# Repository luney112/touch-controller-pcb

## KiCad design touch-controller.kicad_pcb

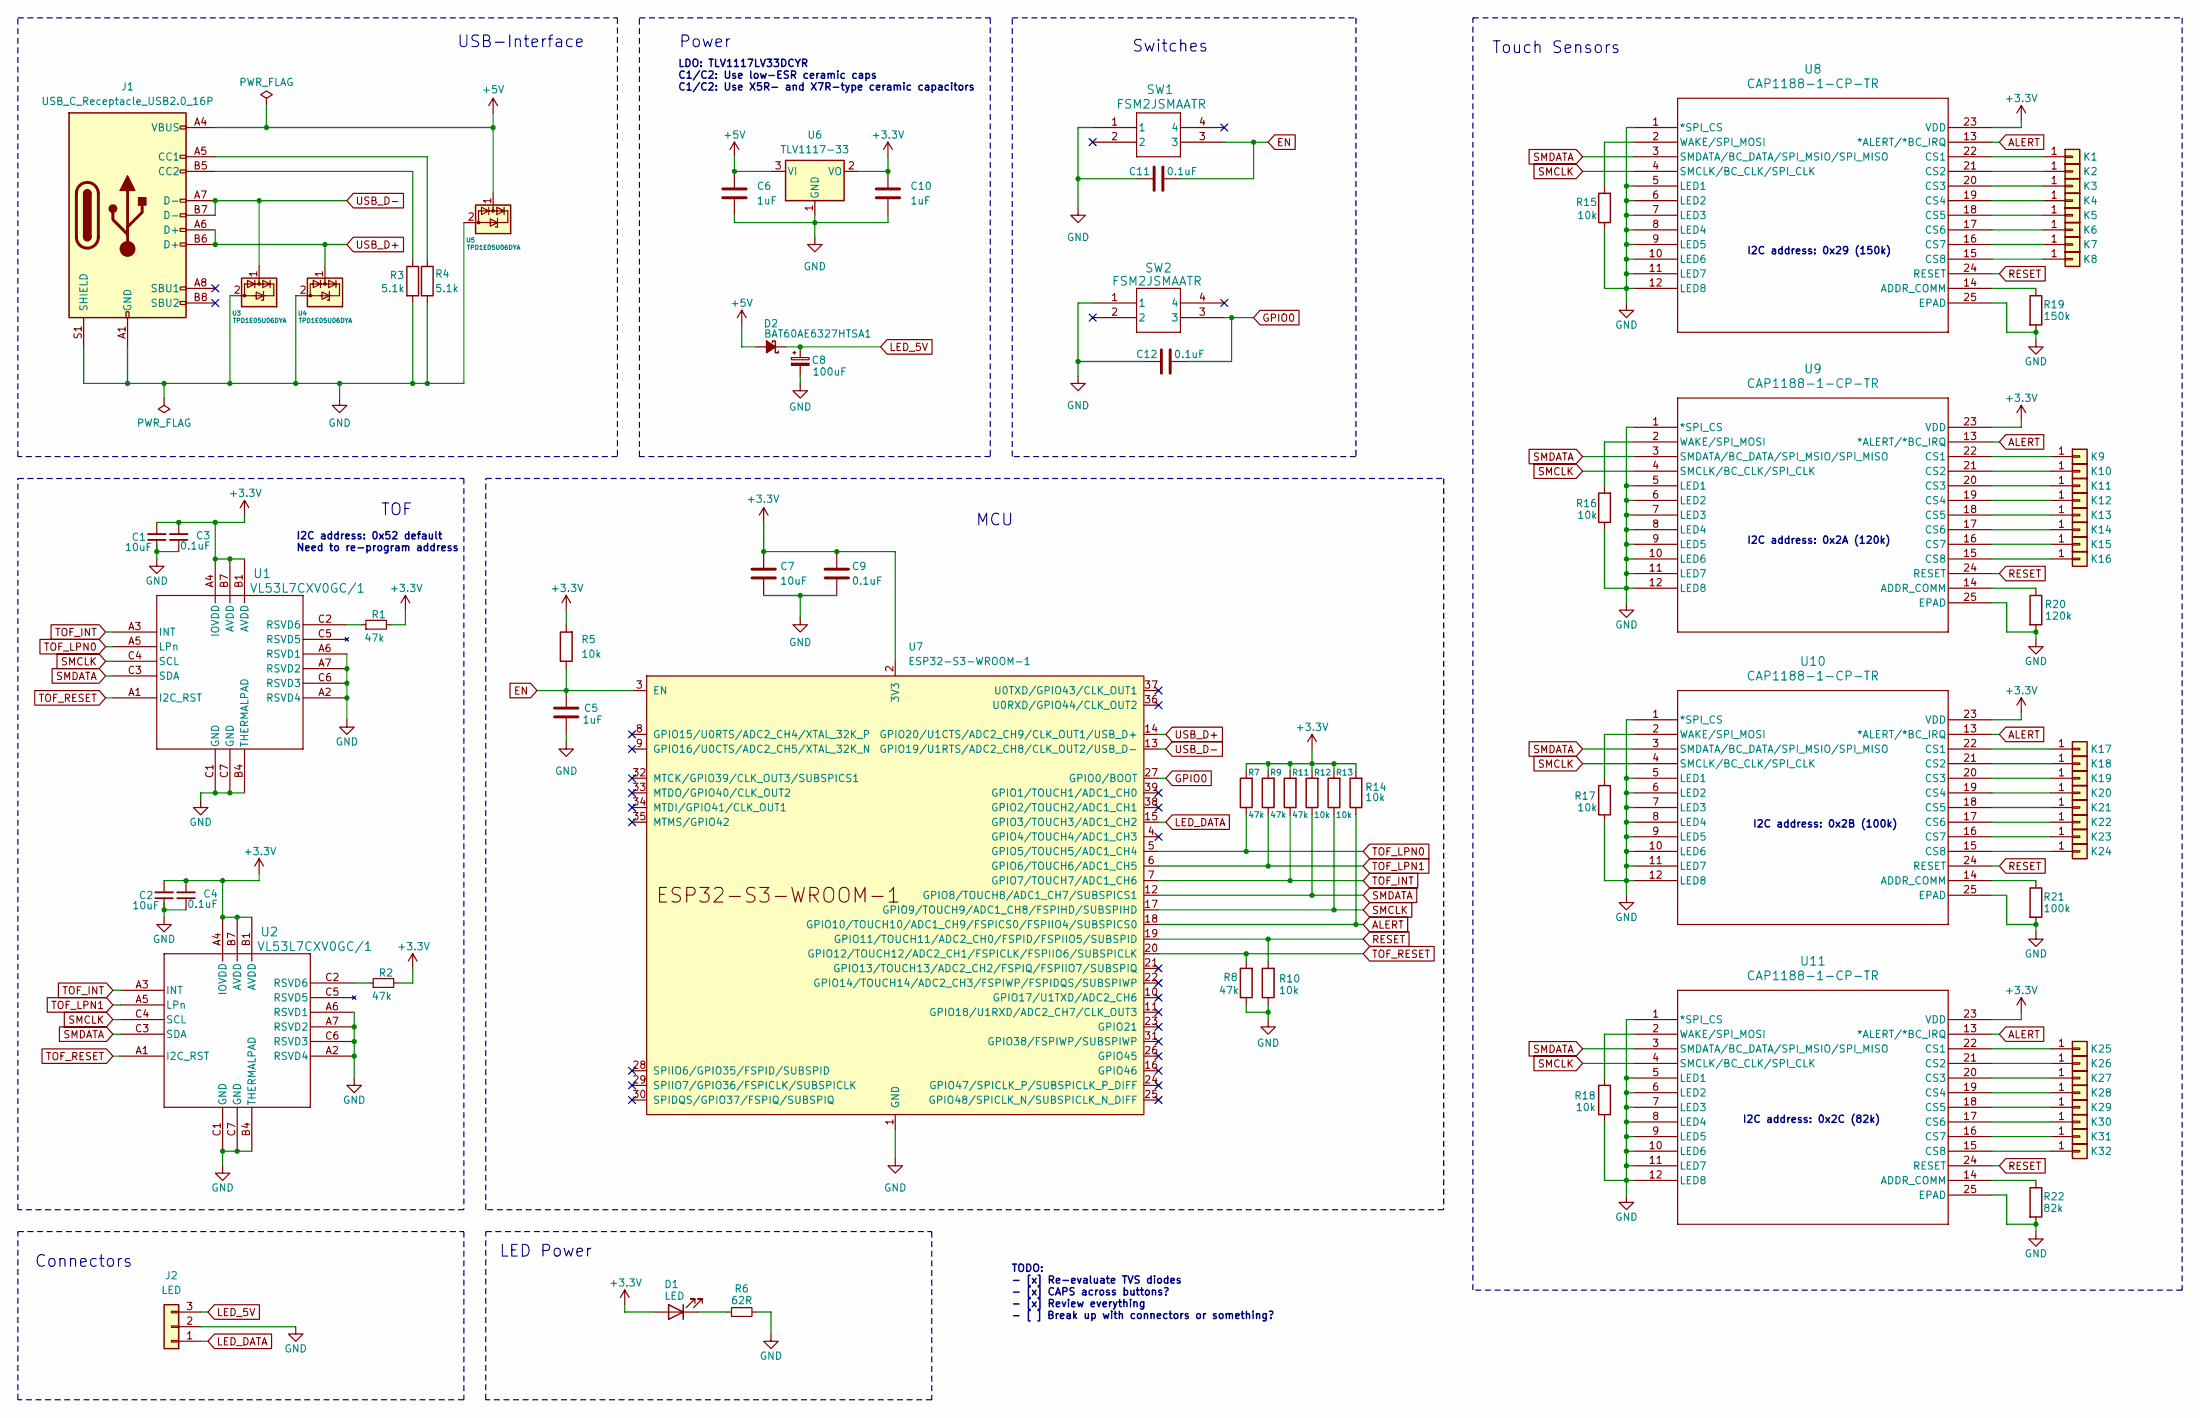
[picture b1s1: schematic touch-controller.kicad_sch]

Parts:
C1, C2, C7: 10uF; C_0805_2012Metric_Pad1.18x1.45mm_HandSolder
C3, C4, C9, C11, C12: 0.1uF; C_0805_2012Metric_Pad1.18x1.45mm_HandSolder
C5, C6, C10: 1uF; C_0805_2012Metric_Pad1.18x1.45mm_HandSolder
C8: 100uF; CP_Elec_6.3x5.8
D1: LED; LED_0805_2012Metric_Pad1.15x1.40mm_HandSolder
D2: BAT60AE6327HTSA1; D_SOD-323_HandSoldering
J1: USB_C_Receptacle_USB2.0_16P; USB_C_Receptacle_GCT_USB4105-xx-A_16P_TopMnt_Horizontal
J2: LED; SolderWire-0.75sqmm_1x03_P4.8mm_D1.25mm_OD2.3mm_Relief
K1, K2, K3, K4, K5, K6, K7, K8, K9, K10, K11, K12, K13, K14, K15, K16, K17, K18, K19, K20, K21, K22, K23, K24, K25, K26, K27, K28, K29, K30, K31, K32: Conn_01x01; TouchKey_Standard
R1, R2, R7, R8, R9, R11: 47k; R_0805_2012Metric_Pad1.20x1.40mm_HandSolder
R3, R4: 5.1k; R_0805_2012Metric_Pad1.20x1.40mm_HandSolder
R5, R10, R12, R13, R14, R15, R16, R17, R18: 10k; R_0805_2012Metric_Pad1.20x1.40mm_HandSolder
R6: 62R; R_0805_2012Metric_Pad1.20x1.40mm_HandSolder
R19: 150k; R_0805_2012Metric_Pad1.20x1.40mm_HandSolder
R20: 120k; R_0805_2012Metric_Pad1.20x1.40mm_HandSolder
R21: 100k; R_0805_2012Metric_Pad1.20x1.40mm_HandSolder
R22: 82k; R_0805_2012Metric_Pad1.20x1.40mm_HandSolder
SW1, SW2: FSM2JSMAATR; SWITCH_FSM2JSMAA_TYC
U1, U2: VL53L7CXV0GC/1; LGA16_OPTICAL-LINER_STM
U3, U4, U5: TPD1E05U06DYA; D_SOD-523
U6: TLV1117-33; SOT-223-3_TabPin2
U7: ESP32-S3-WROOM-1
U8, U9, U10, U11: CAP1188-1-CP-TR; QFN24_4X4MC_MCH

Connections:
+3.3V: C1.2, C2.2, C3.2, C4.2, C7.2, C9.2, C10.1, D1.2 (A), R1.2, R2.2, R5.2, R7.2, R9.2, R11.2, R12.2, R13.2, R14.2, U1.A4 (IOVDD), U1.B1 (AVDD), U1.B7 (AVDD), U2.A4 (IOVDD), U2.B1 (AVDD), U2.B7 (AVDD), U6.2 (VO), U7.2 (3V3), U8.23 (VDD), U9.23 (VDD), U10.23 (VDD), U11.23 (VDD)
+5V: C6.1, D2.2 (A), J1.A4 (VBUS), J1.A9 (VBUS), J1.B4 (VBUS), J1.B9 (VBUS), U5.1 (I/O), U6.3 (VI)
ALERT: R14.1, U7.18 (GPIO10/TOUCH10/ADC1_CH9/FSPICS0/FSPIIO4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), U8.13 (*ALERT/*BC_IRQ), U9.13 (*ALERT/*BC_IRQ), U10.13 (*ALERT/*BC_IRQ), U11.13 (*ALERT/*BC_IRQ)
EN: C5.1, C11.1, R5.1, SW1.3, U7.3 (EN)
GND: C1.1, C2.1, C3.1, C4.1, C5.2, C6.2, C7.1, C8.2, C9.1, C10.2, C11.2, C12.2, J1.A1 (GND), J1.A12 (GND), J1.B1 (GND), J1.B12 (GND), J1.S1 (SHIELD), J2.2, R3.2, R4.2, R6.2, R8.1, R10.1, R15.1, R16.1, R17.1, R18.1, R19.2, R20.2, R21.2, R22.2, SW1.1, SW2.1, U1.A2 (RSVD4), U1.A6 (RSVD1), U1.A7 (RSVD2), U1.B4 (THERMALPAD), U1.C1 (GND), U1.C6 (RSVD3), U1.C7 (GND), U2.A2 (RSVD4), U2.A6 (RSVD1), U2.A7 (RSVD2), U2.B4 (THERMALPAD), U2.C1 (GND), U2.C6 (RSVD3), U2.C7 (GND), U3.2 (GND), U4.2 (GND), U5.2 (GND), U6.1 (GND), U7.1 (GND), U7.40 (GND), U7.41 (GND), U8.1 (*SPI_CS), U8.5 (LED1), U8.6 (LED2), U8.7 (LED3), U8.8 (LED4), U8.9 (LED5), U8.10 (LED6), U8.11 (LED7), U8.12 (LED8), U8.25 (EPAD), U9.1 (*SPI_CS), U9.5 (LED1), U9.6 (LED2), U9.7 (LED3), U9.8 (LED4), U9.9 (LED5), U9.10 (LED6), U9.11 (LED7), U9.12 (LED8), U9.25 (EPAD), U10.1 (*SPI_CS), U10.5 (LED1), U10.6 (LED2), U10.7 (LED3), U10.8 (LED4), U10.9 (LED5), U10.10 (LED6), U10.11 (LED7), U10.12 (LED8), U10.25 (EPAD), U11.1 (*SPI_CS), U11.5 (LED1), U11.6 (LED2), U11.7 (LED3), U11.8 (LED4), U11.9 (LED5), U11.10 (LED6), U11.11 (LED7), U11.12 (LED8), U11.25 (EPAD)
GPIO0: C12.1, SW2.3, U7.27 (GPIO0/BOOT)
LED_5V: C8.1, D2.1 (K), J2.3
LED_DATA: J2.1, U7.15 (GPIO3/TOUCH3/ADC1_CH2)
unnamed: D1.1 (K), R6.1
unnamed: J1.A5 (CC1), R4.1
unnamed: J1.B5 (CC2), R3.1
unnamed: K1.1, U8.22 (CS1)
unnamed: K2.1, U8.21 (CS2)
unnamed: K3.1, U8.20 (CS3)
unnamed: K4.1, U8.19 (CS4)
unnamed: K5.1, U8.18 (CS5)
unnamed: K6.1, U8.17 (CS6)
unnamed: K7.1, U8.16 (CS7)
unnamed: K8.1, U8.15 (CS8)
unnamed: K9.1, U9.22 (CS1)
unnamed: K10.1, U9.21 (CS2)
unnamed: K11.1, U9.20 (CS3)
unnamed: K12.1, U9.19 (CS4)
unnamed: K13.1, U9.18 (CS5)
unnamed: K14.1, U9.17 (CS6)
unnamed: K15.1, U9.16 (CS7)
unnamed: K16.1, U9.15 (CS8)
unnamed: K17.1, U10.22 (CS1)
unnamed: K18.1, U10.21 (CS2)
unnamed: K19.1, U10.20 (CS3)
unnamed: K20.1, U10.19 (CS4)
unnamed: K21.1, U10.18 (CS5)
unnamed: K22.1, U10.17 (CS6)
unnamed: K23.1, U10.16 (CS7)
unnamed: K24.1, U10.15 (CS8)
unnamed: K25.1, U11.22 (CS1)
unnamed: K26.1, U11.21 (CS2)
unnamed: K27.1, U11.20 (CS3)
unnamed: K28.1, U11.19 (CS4)
unnamed: K29.1, U11.18 (CS5)
unnamed: K30.1, U11.17 (CS6)
unnamed: K31.1, U11.16 (CS7)
unnamed: K32.1, U11.15 (CS8)
unnamed: R1.1, U1.C2 (RSVD6)
unnamed: R2.1, U2.C2 (RSVD6)
unnamed: R19.1, U8.14 (ADDR_COMM)
unnamed: R15.2, U8.2 (WAKE/SPI_MOSI)
unnamed: R20.1, U9.14 (ADDR_COMM)
unnamed: R16.2, U9.2 (WAKE/SPI_MOSI)
unnamed: R21.1, U10.14 (ADDR_COMM)
unnamed: R17.2, U10.2 (WAKE/SPI_MOSI)
unnamed: R22.1, U11.14 (ADDR_COMM)
unnamed: R18.2, U11.2 (WAKE/SPI_MOSI)
RESET: R10.2, U7.19 (GPIO11/TOUCH11/ADC2_CH0/FSPID/FSPIIO5/S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), U8.24 (RESET), U9.24 (RESET), U10.24 (RESET), U11.24 (RESET)
SMCLK: R13.1, U1.C4 (SCL), U2.C4 (SCL), U7.17 (GPIO9/TOUCH9/ADC1_CH8/FSPIHD/SUBSPIHD), U8.4 (SMCLK/BC_CLK/SPI_CLK), U9.4 (SMCLK/BC_CLK/SPI_CLK), U10.4 (SMCLK/BC_CLK/SPI_CLK), U11.4 (SMCLK/BC_CLK/SPI_CLK)
SMDATA: R12.1, U1.C3 (SDA), U2.C3 (SDA), U7.12 (GPIO8/TOUCH8/ADC1_CH7/SUBSPICS1), U8.3 (SMDATA/BC_DATA/SPI_MSIO/SPI_MISO), U9.3 (SMDATA/BC_DATA/SPI_MSIO/SPI_MISO), U10.3 (SMDATA/BC_DATA/SPI_MSIO/SPI_MISO), U11.3 (SMDATA/BC_DATA/SPI_MSIO/SPI_MISO)
TOF_INT: R11.1, U1.A3 (INT), U2.A3 (INT), U7.7 (GPIO7/TOUCH7/ADC1_CH6)
TOF_LPN0: R7.1, U1.A5 (LPn), U7.5 (GPIO5/TOUCH5/ADC1_CH4)
TOF_LPN1: R9.1, U2.A5 (LPn), U7.6 (GPIO6/TOUCH6/ADC1_CH5)
TOF_RESET: R8.2, U1.A1 (I2C_RST), U2.A1 (I2C_RST), U7.20 (GPIO12/TOUCH12/ADC2_CH1/FSPICLK/FSPIIO6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)
USB_D+: J1.A6 (D+), J1.B6 (D+), U4.1 (I/O), U7.14 (GPIO20/U1CTS/ADC2_CH9/CLK_OUT1/USB_D+)
USB_D-: J1.A7 (D-), J1.B7 (D-), U3.1 (I/O), U7.13 (GPIO19/U1RTS/ADC2_CH8/CLK_OUT2/USB_D-)

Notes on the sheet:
I2C address: 0x52 default Need to re-program address
I2C address: 0x2C (82k)
TODO: - [x] Re-evaluate TVS diodes - [x] CAPS across buttons? - [x] Review everything - [ ] Break up with connectors or something?
LED Power
I2C address: 0x2B (100k)
Connectors
MCU
LDO: TLV1117LV33DCYR C1/C2: Use low-ESR ceramic caps C1/C2: Use X5R- and X7R-type ceramic capacitors
I2C address: 0x29 (150k)
TOF
USB-Interface
Power
I2C address: 0x2A (120k)
Touch Sensors
Switches

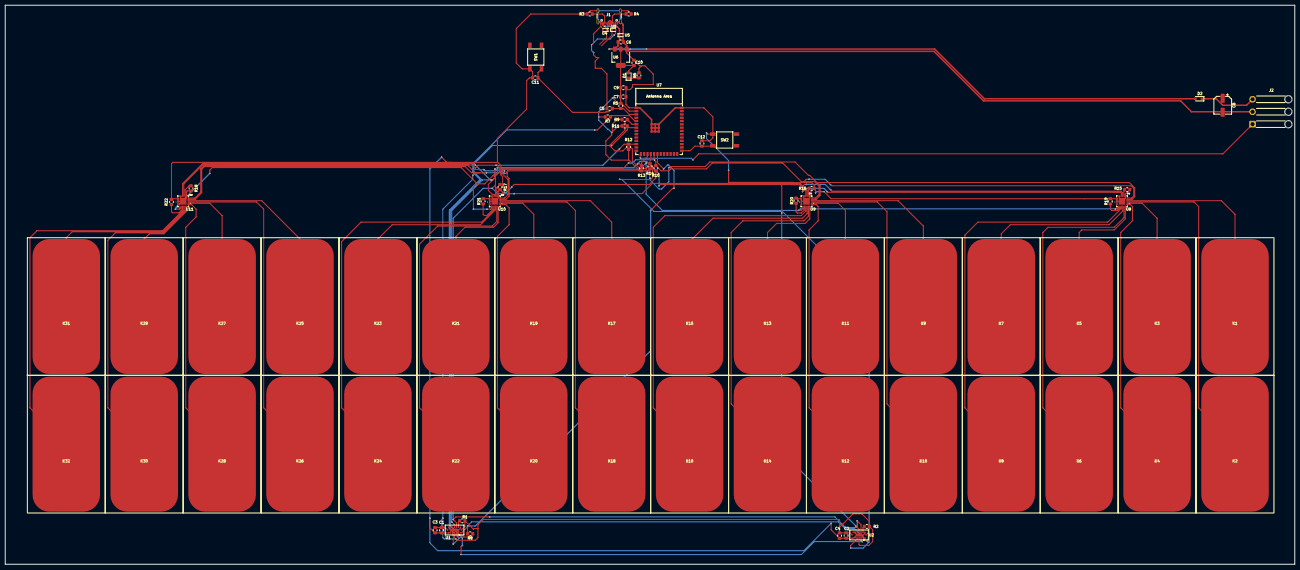
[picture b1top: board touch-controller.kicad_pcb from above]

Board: 2 copper layers, 496.5 x 215.2 mm, 83 parts (0 on the bottom side), 62 nets.

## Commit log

2024-11-29 Add ToF sensor & other changes (pcb broken)
2024-11-29 Update gitignore
2024-11-29 Rewrite line endings
2024-11-29 Add ToF sensor
2024-12-03 Partial pcb fix
